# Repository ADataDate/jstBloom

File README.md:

# jstBloom
A breakout board for the JST connector commonly used with batteries and a switch.

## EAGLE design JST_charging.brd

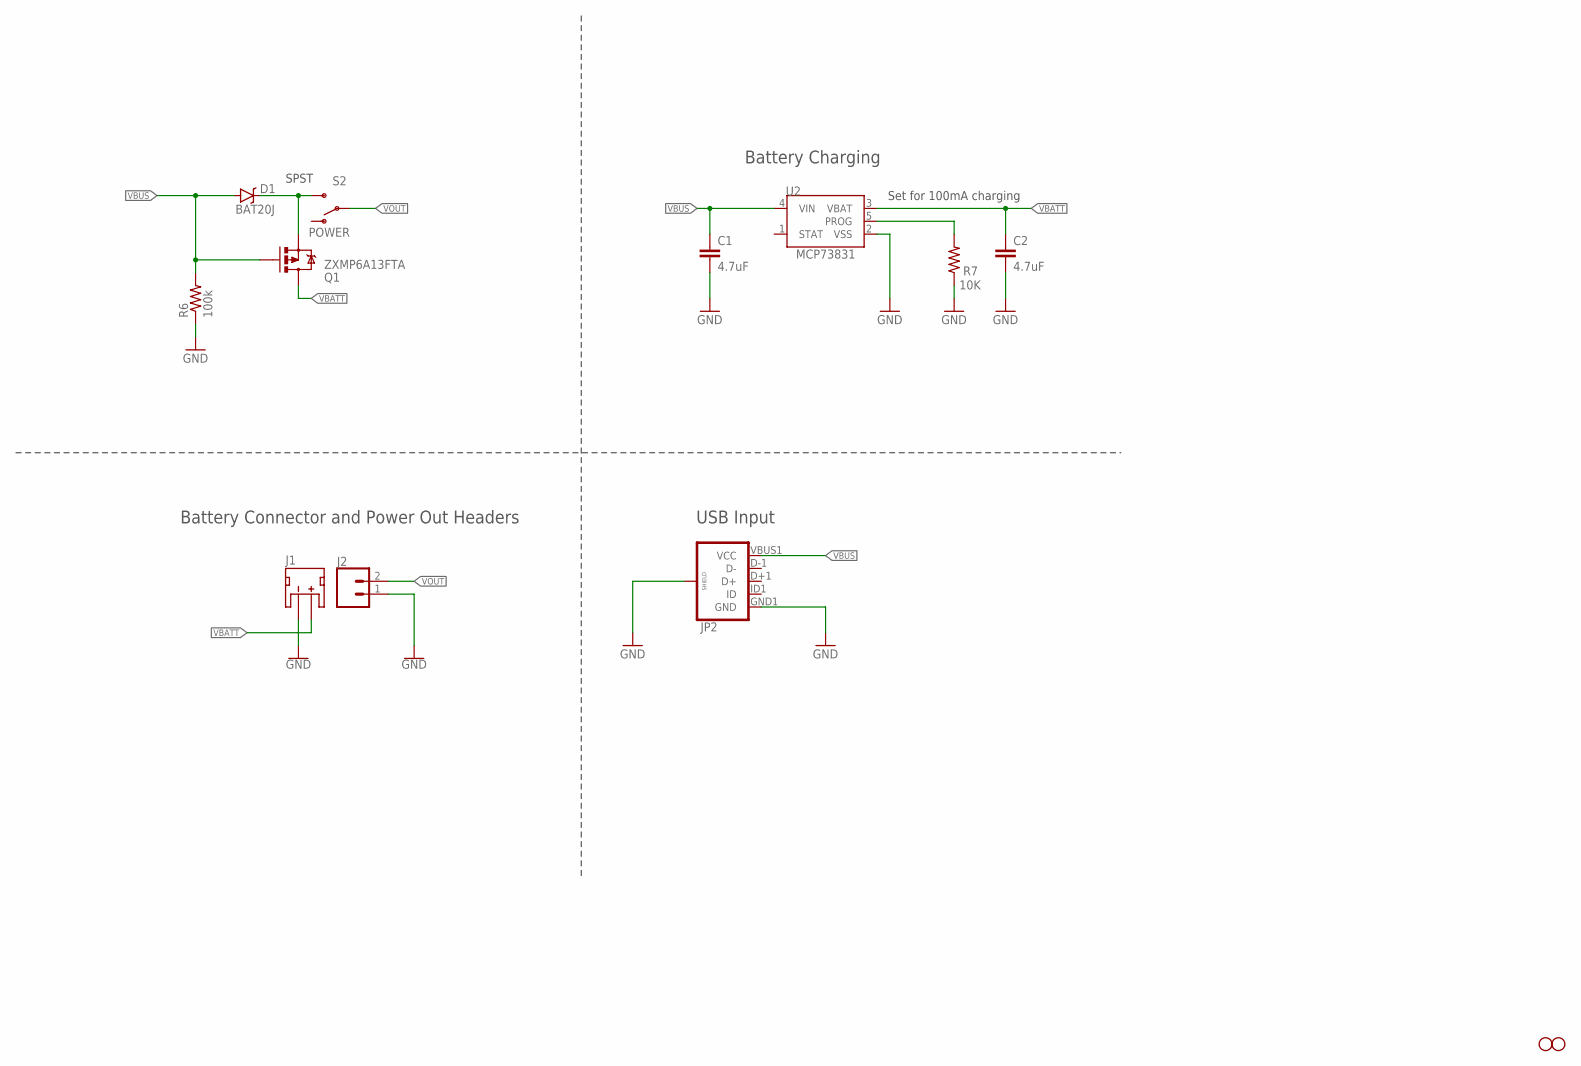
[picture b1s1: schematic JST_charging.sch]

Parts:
C1, C2: 4.7uF; 0603-CAP
D1: BAT20J; SOD-323
H1, H2: STAND-OFFTIGHT; STAND-OFF-TIGHT
J1: JST_2MM_MALE; JST-2-SMD
J2: CONN_021X02_NO_SILK; 1X02_NO_SILK
JP2: USB_MICROB_PLUGCONN-11752; USB-B-MICRO-SMD_V03
Q1: ZXMP6A13FTA; SOT23-3
R6: 100k; 0603-RES
R7: 10K; 0603-RES
S2: POWER; SWITCH-SPST-SMD-A
U2: MCP73831; SOT23-5

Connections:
GND: C1.2, C2.2, J1.1 (-), J2.1, JP2.GND1 (GND), JP2.SHIELD1 (SHIELD), JP2.SHIELD2 (SHIELD), JP2.SHIELD3 (SHIELD), R6.1, R7.1, U2.2 (VSS)
INMOSFET: D1.C, Q1.2 (S), S2.3 (S)
PROG: R7.2, U2.5 (PROG)
VBATT: C2.1, J1.2 (+), Q1.3 (D), U2.3 (VBAT)
VBUS: C1.1, D1.A, JP2.VBUS1 (VCC), Q1.1 (G), R6.2, U2.4 (VIN)
VOUT: J2.2, S2.2

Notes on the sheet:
Set for 100mA charging
SPST
Battery Connector and Power Out Headers
USB Input
Battery Charging

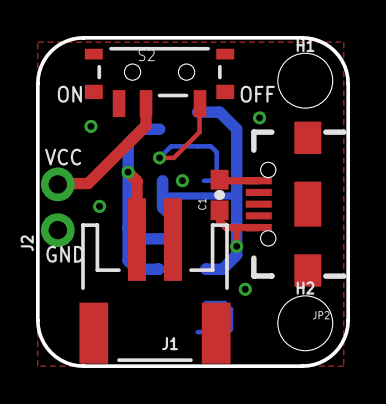
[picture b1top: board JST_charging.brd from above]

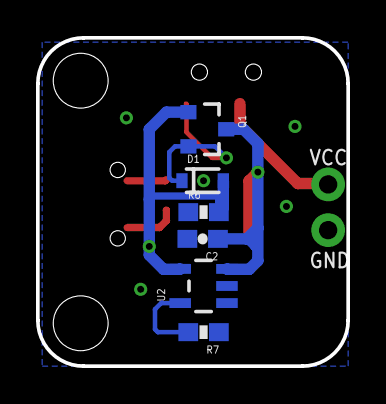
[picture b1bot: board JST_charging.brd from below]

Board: 2 copper layers, 17.2 x 18.2 mm, 13 parts (6 on the bottom side), 6 nets.

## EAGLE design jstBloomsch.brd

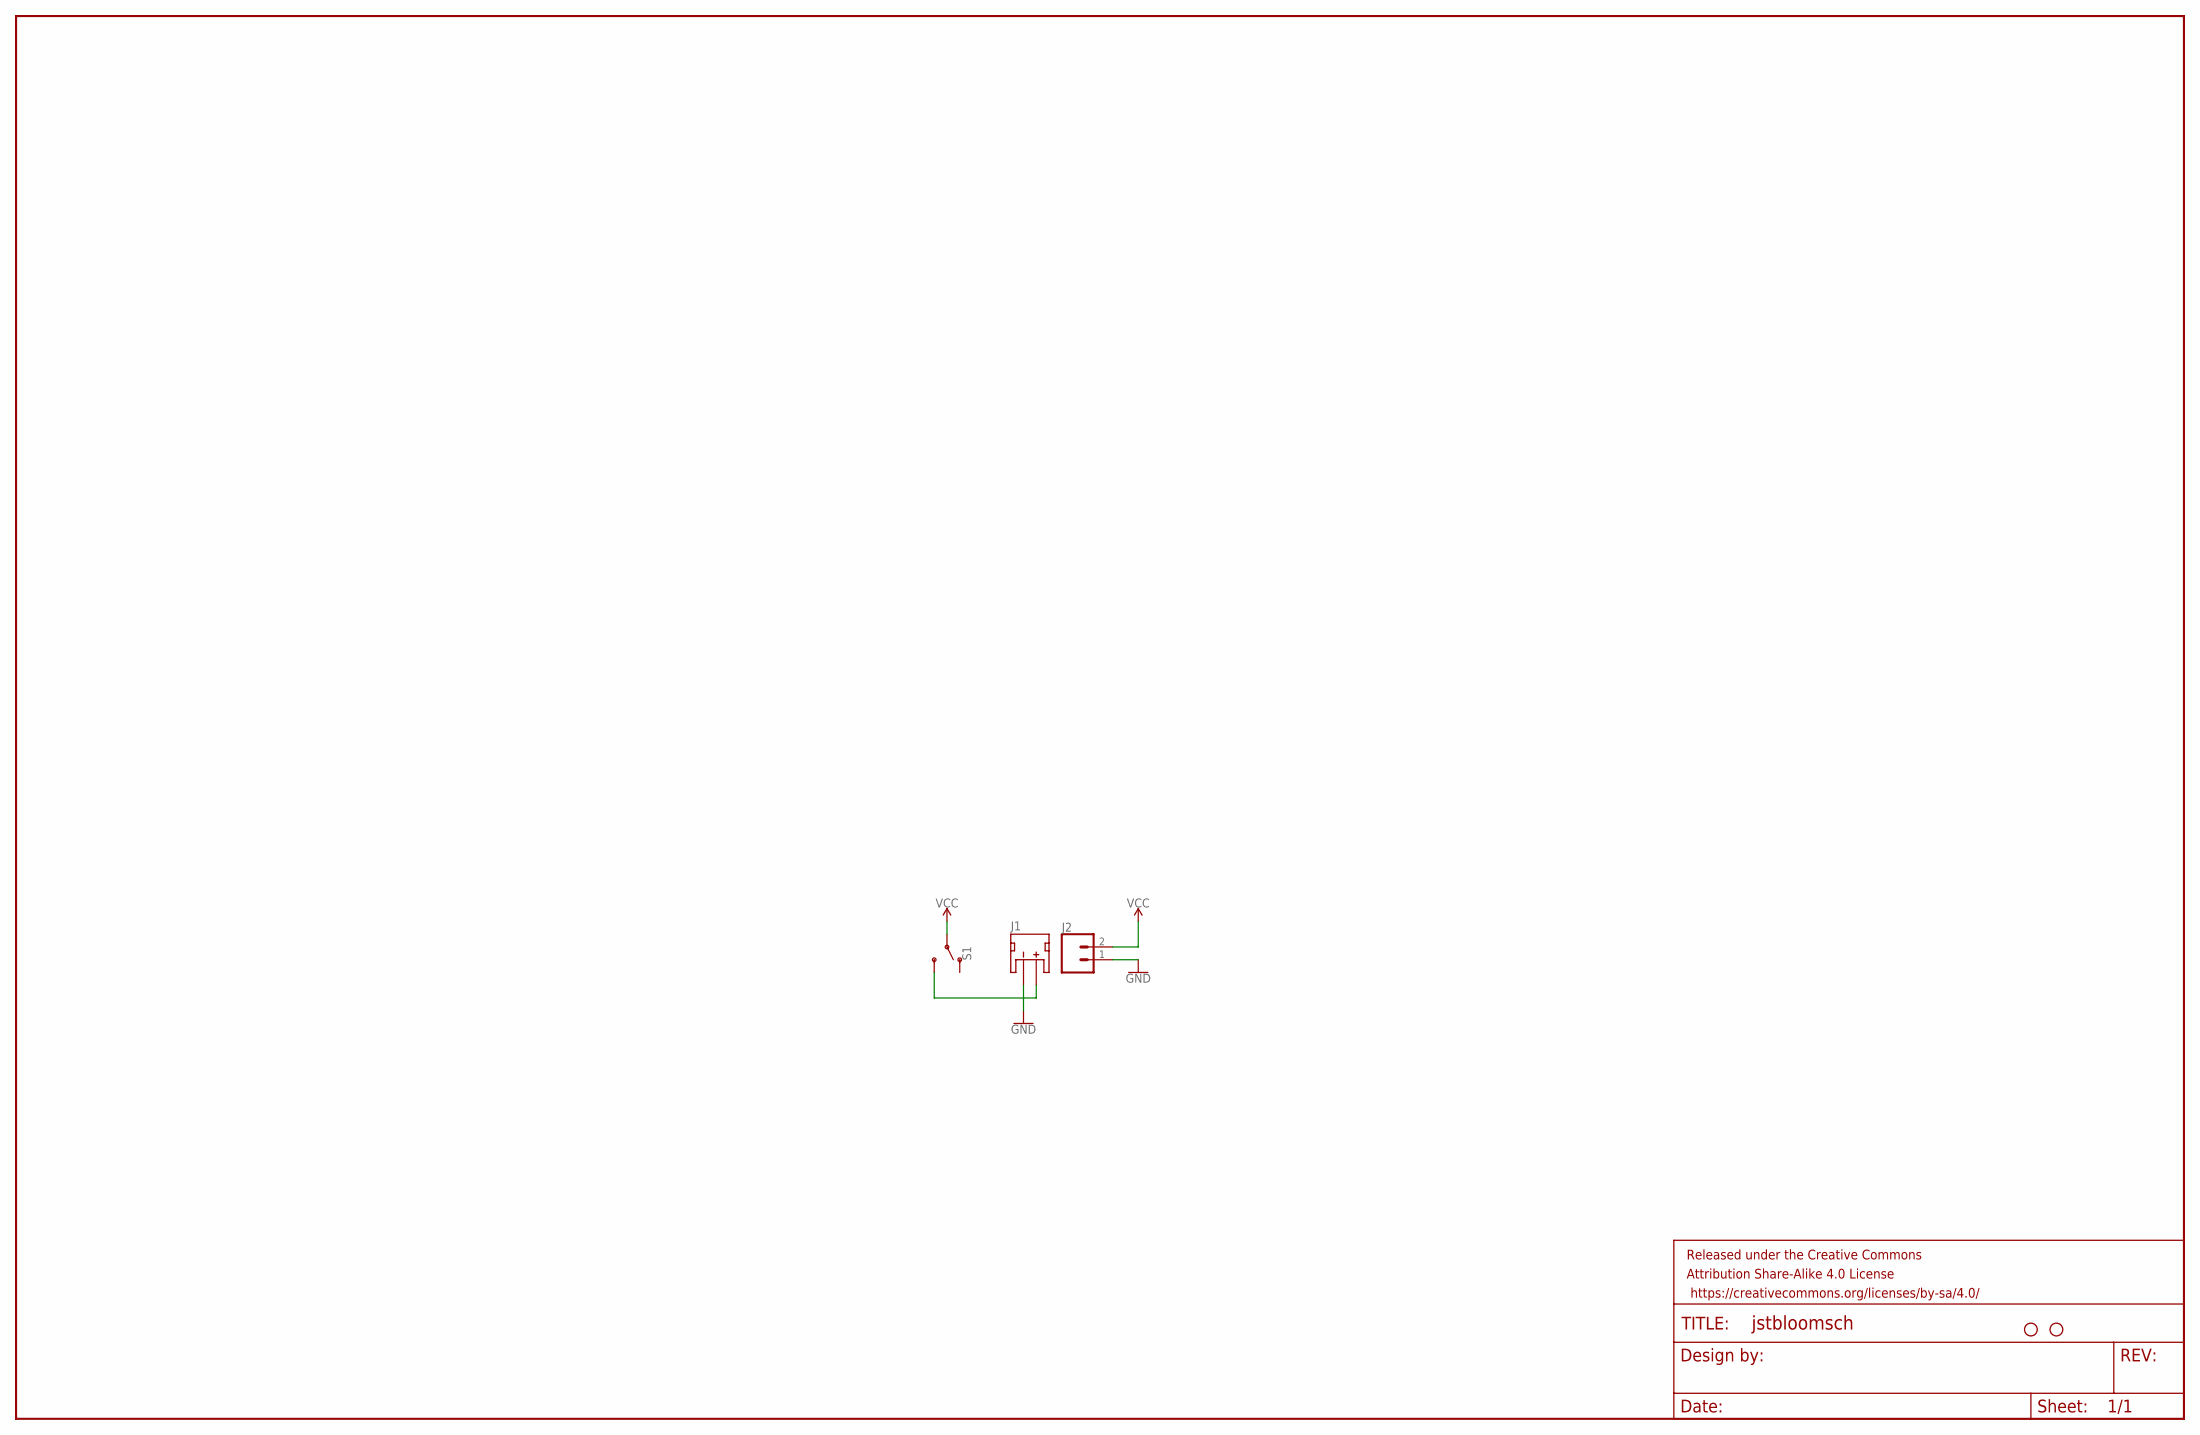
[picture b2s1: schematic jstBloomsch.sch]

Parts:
FRAME1: FRAME-LEDGER; CREATIVE_COMMONS
H1, H2: STAND-OFFTIGHT; STAND-OFF-TIGHT
J1: JST_2MM_MALE; JST-2-SMD
J2: CONN_021X02_NO_SILK; 1X02_NO_SILK
S1: SWITCH-SPDT-SMD-RIGHT-ANGLE; SWITCH_SPST_SMD_A

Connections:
GND: J1.1 (-), J2.1
unnamed: J1.2 (+), S1.3 (S)
VCC: J2.2, S1.2

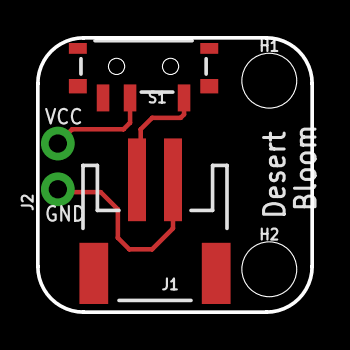
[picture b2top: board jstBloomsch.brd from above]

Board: 2 copper layers, 15.2 x 15.2 mm, 6 parts (0 on the bottom side), 3 nets.

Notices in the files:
parts and their libraries:
SparkFun-Connectors: Licensing: Creative Commons ShareAlike 4.0 International - https://creativecommons.org/licenses/by-sa/4.0
SparkFun-Passives: Licensing: CC v3.0 Share-Alike You are welcome to use this library for commercial purposes.
SparkFun-Aesthetics: Released under the Creative Commons
